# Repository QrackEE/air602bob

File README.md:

# ABOUT

Simple breakout board for Air602 WiSoM module. [Seeed shop page with specifications](https://www.seeedstudio.com/Air602-WiFi-Module-p-3139.html) shows technical details (including dimensions and pinout), diagrams and pictures of this ~$2 piece.  
For additional $1, [Development Board](https://www.seeedstudio.com/Air602-WiFi-Development-Board-p-3140.html) with USB connection is available.  
For getting started, see [Novakov repositories](https://github.com/Novakov):  
- https://github.com/Novakov/air602-hello-world
- https://github.com/Novakov/W600_SDK

# DESIGN REQUIREMENTS

Board requirements definition is as follows:

- breakout castellations to breadboard-compatible goldpins,
- pinout compatible with the module itself (incl. optional antenna routing through goldpin),
- antenna pad, (u.fl) connector or on-board (chip/F) antenna,
- at least few boards maufactured,
- hardware development in freely available package, i.e Kicad.

# HARDWARE DESCRIPTION

The design is really simple - main part is Air602 module, from which all pins are routed to goldpin headers which allow to use module with standard breadboard.
Single MLCC is provided for power supply rail to the module.
On breakout board, PI antenna matching network footprints are provided. Initially capacitors can be left unpopulated and inductance can be replaced with 0 Ohm resistor. It is worth to note that Air602 itself has some L antenna matching network with only series element populated.  
Additionally, multiple antenna options are provided - by default only XA1 (u.fl/IPX connector) and XA2 (custom non-plated through-hole footprint) are available. Other options are ANT1 Printed Inverted F Antenna (PIFA) by soldering JP2 solder jumper and routing signal to J2-2 goldpin header pin by soldering JP1 solder jumper. The latest is straight from Air602 module and is least advised.

## Connecting Antenna to Goldpin Header Pin JP2-2

This method is not really advised with provided hardware design, but if this option is required (either by application or because other antenna means provided by breakout fail) following actions must be taken:

- JP1 must be soldered,
- C2 must be unpopulated,
- L1 must be unpopulated,
- It is advised to cut the feedline track which goes to the PI matching circuit near JP1 to reduce stub

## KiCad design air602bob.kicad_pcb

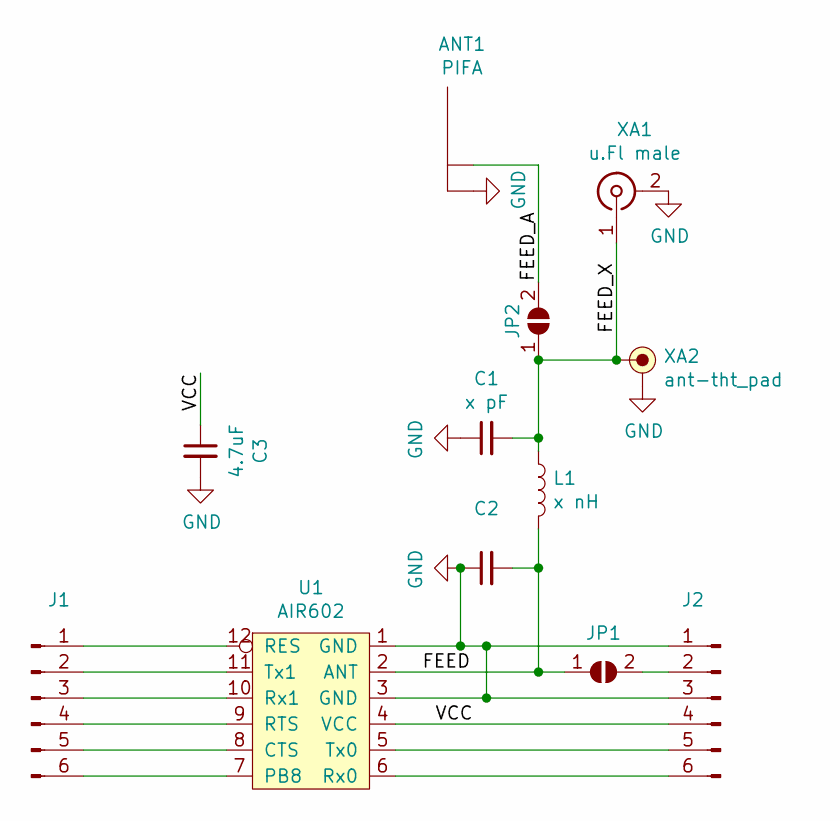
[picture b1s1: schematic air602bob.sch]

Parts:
ANT1: PIFA; Texas_SWRA117D_2.4GHz_Left
C1, C2: x pF; C_0402_1005Metric
C3: 4.7uF; C_0603_1608Metric_Pad1.05x0.95mm_HandSolder
J1, J2: Conn_01x06_Male; PinHeader_1x06_P2.54mm_Vertical
JP1, JP2: SolderJumper_2_Open; SolderJumper-2_P0.6mm_Open_RoundedPad0.5x0.8mm
L1: x nH; L_0402_1005Metric
U1: AIR602
XA1: u.Fl male; U.FL_Molex_MCRF_73412-0110_Vertical
XA2: ant-tht_pad; ant-via_tht

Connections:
/FEED: C2.2, JP1.1 (A), L1.2, U1.2 (ANT)
/FEED_A: ANT1.1 (ANT), JP2.2 (B)
/FEED_X: C1.2, JP2.1 (A), L1.1, XA1.1 (In), XA2.1
/VCC: C3.1, J2.4, U1.4 (VCC)
GND: ANT1.2 (REF), C1.1, C2.1, C3.2, J2.1, J2.3, U1.1 (GND), U1.3 (GND), XA1.2 (Ext), XA2.2
unnamed: J1.1, U1.12 (RES)
unnamed: J1.2, U1.11 (Tx1)
unnamed: J1.3, U1.10 (Rx1)
unnamed: J1.4, U1.9 (RTS)
unnamed: J1.5, U1.8 (CTS)
unnamed: J1.6, U1.7 (PB8)
unnamed: J2.2, JP1.2 (B)
unnamed: J2.5, U1.5 (Tx0)
unnamed: J2.6, U1.6 (Rx0)

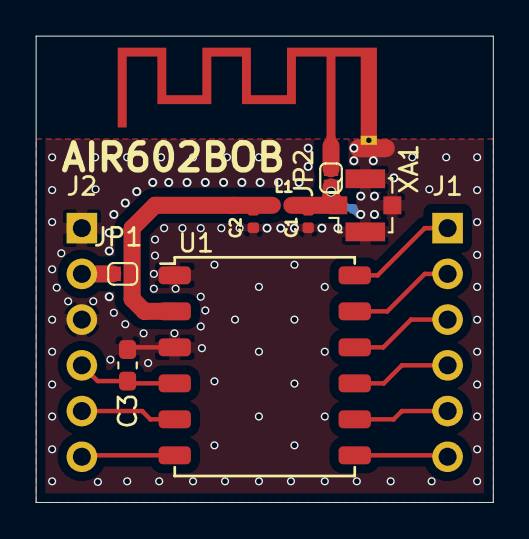
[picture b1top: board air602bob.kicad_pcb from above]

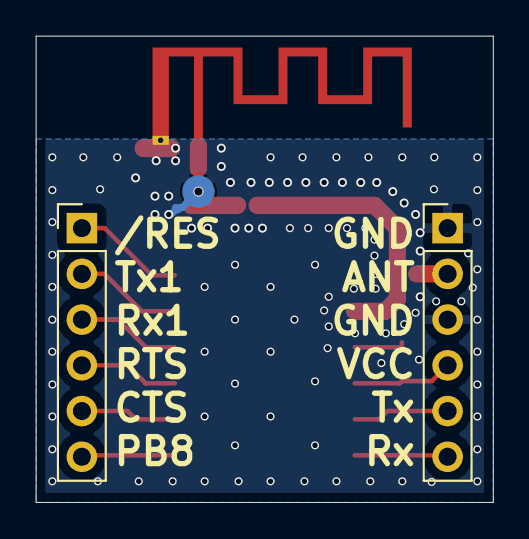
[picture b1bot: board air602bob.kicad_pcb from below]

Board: 2 copper layers, 25.4 x 25.9 mm, 12 parts (2 on the bottom side), 14 nets.

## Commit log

2018-10-30 Initial commit - KiCAD project started
2018-10-30 True development start
2018-10-30 Schematic kind of done, may miss antenna pad, passives, 0R selectors or chip/F anetnna component
2018-10-31 Requirement specification change
2018-11-07 air602 library submodule added from GitHub
2018-11-07 W-L sync check
2018-11-10 Antenna matching PI network added
2018-11-10 Concept finished, request to be evaluated. Needs verification before manufacture order
2018-11-11 Feedline layout changed to not go under Air602 module, custom THT pad added for antenna. README updated.
2018-12-03 Bottom pad for antenna through-hole was not connected after fill repour - mandatory actions taken
2018-12-05 Minor Rx1 track esthetics
2018-12-05 Added Release directory with STEP model and GERBER files for single board and 100x100 9 unit panel
2018-12-14 Feedline width changed to 0.5mm from 0.95mm after using different, more trusty, GCPW calculator
2018-12-16 Power supply decoupling capacitor value inserted
2018-12-23 Notes updated, thermal reliefs for some ground pads added
2018-12-23 Notes updated, thermal reliefs added for easier soldering
2019-01-10 README updated by mentioning Novakov repos
